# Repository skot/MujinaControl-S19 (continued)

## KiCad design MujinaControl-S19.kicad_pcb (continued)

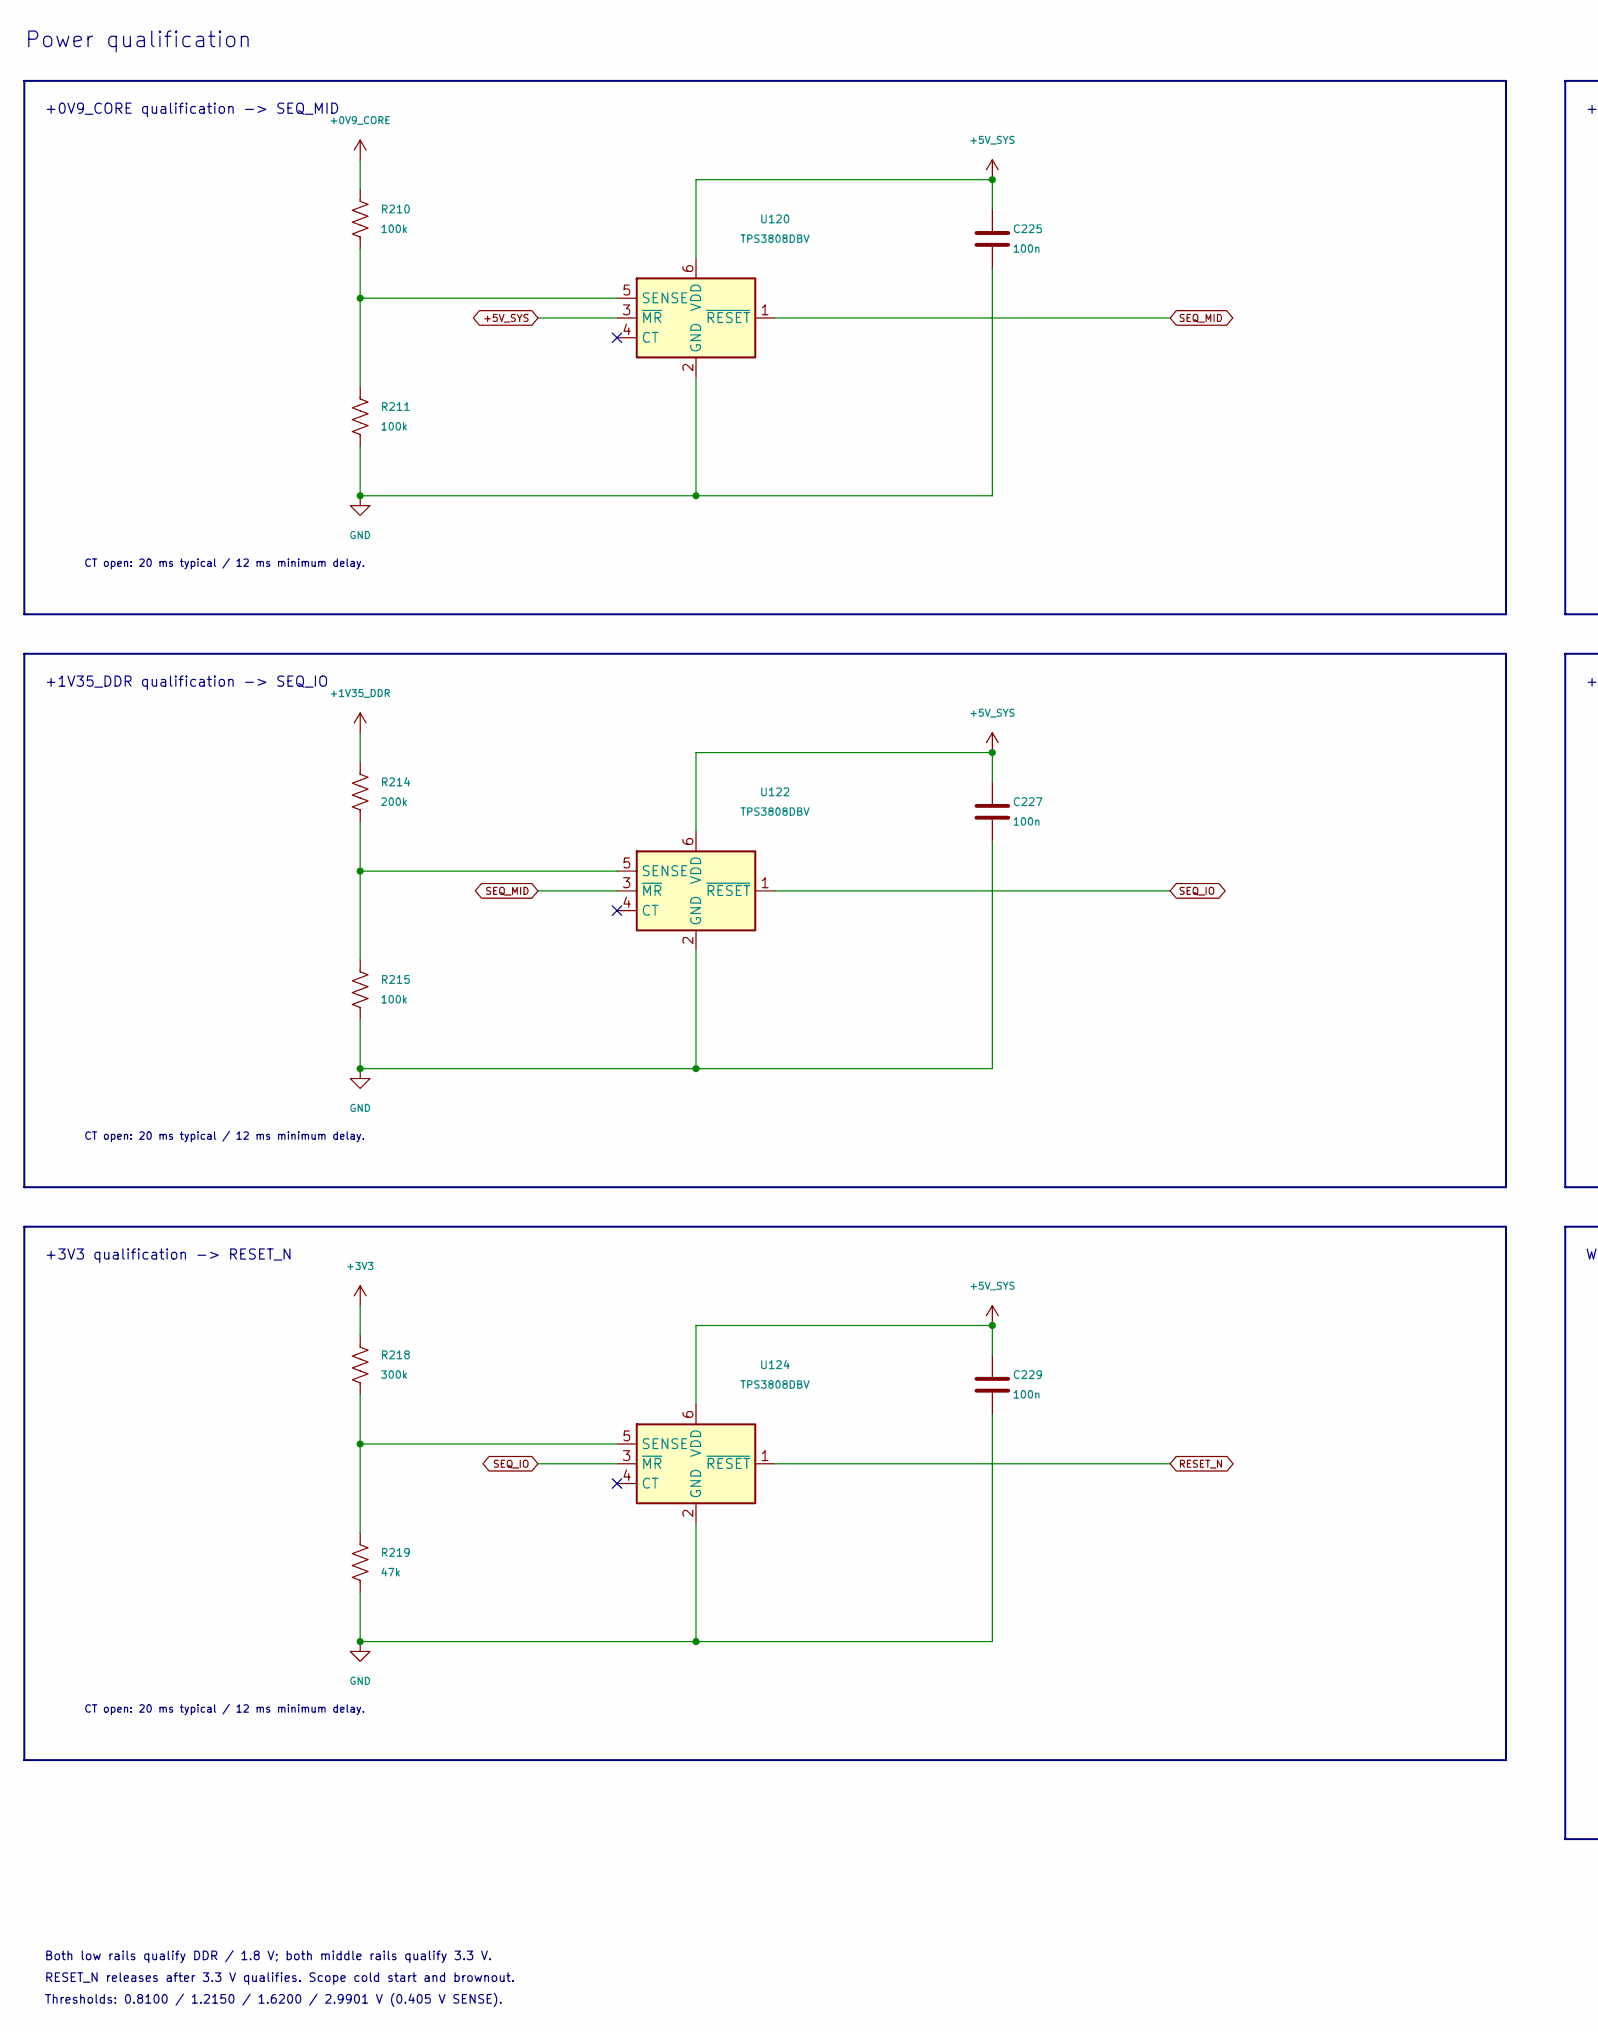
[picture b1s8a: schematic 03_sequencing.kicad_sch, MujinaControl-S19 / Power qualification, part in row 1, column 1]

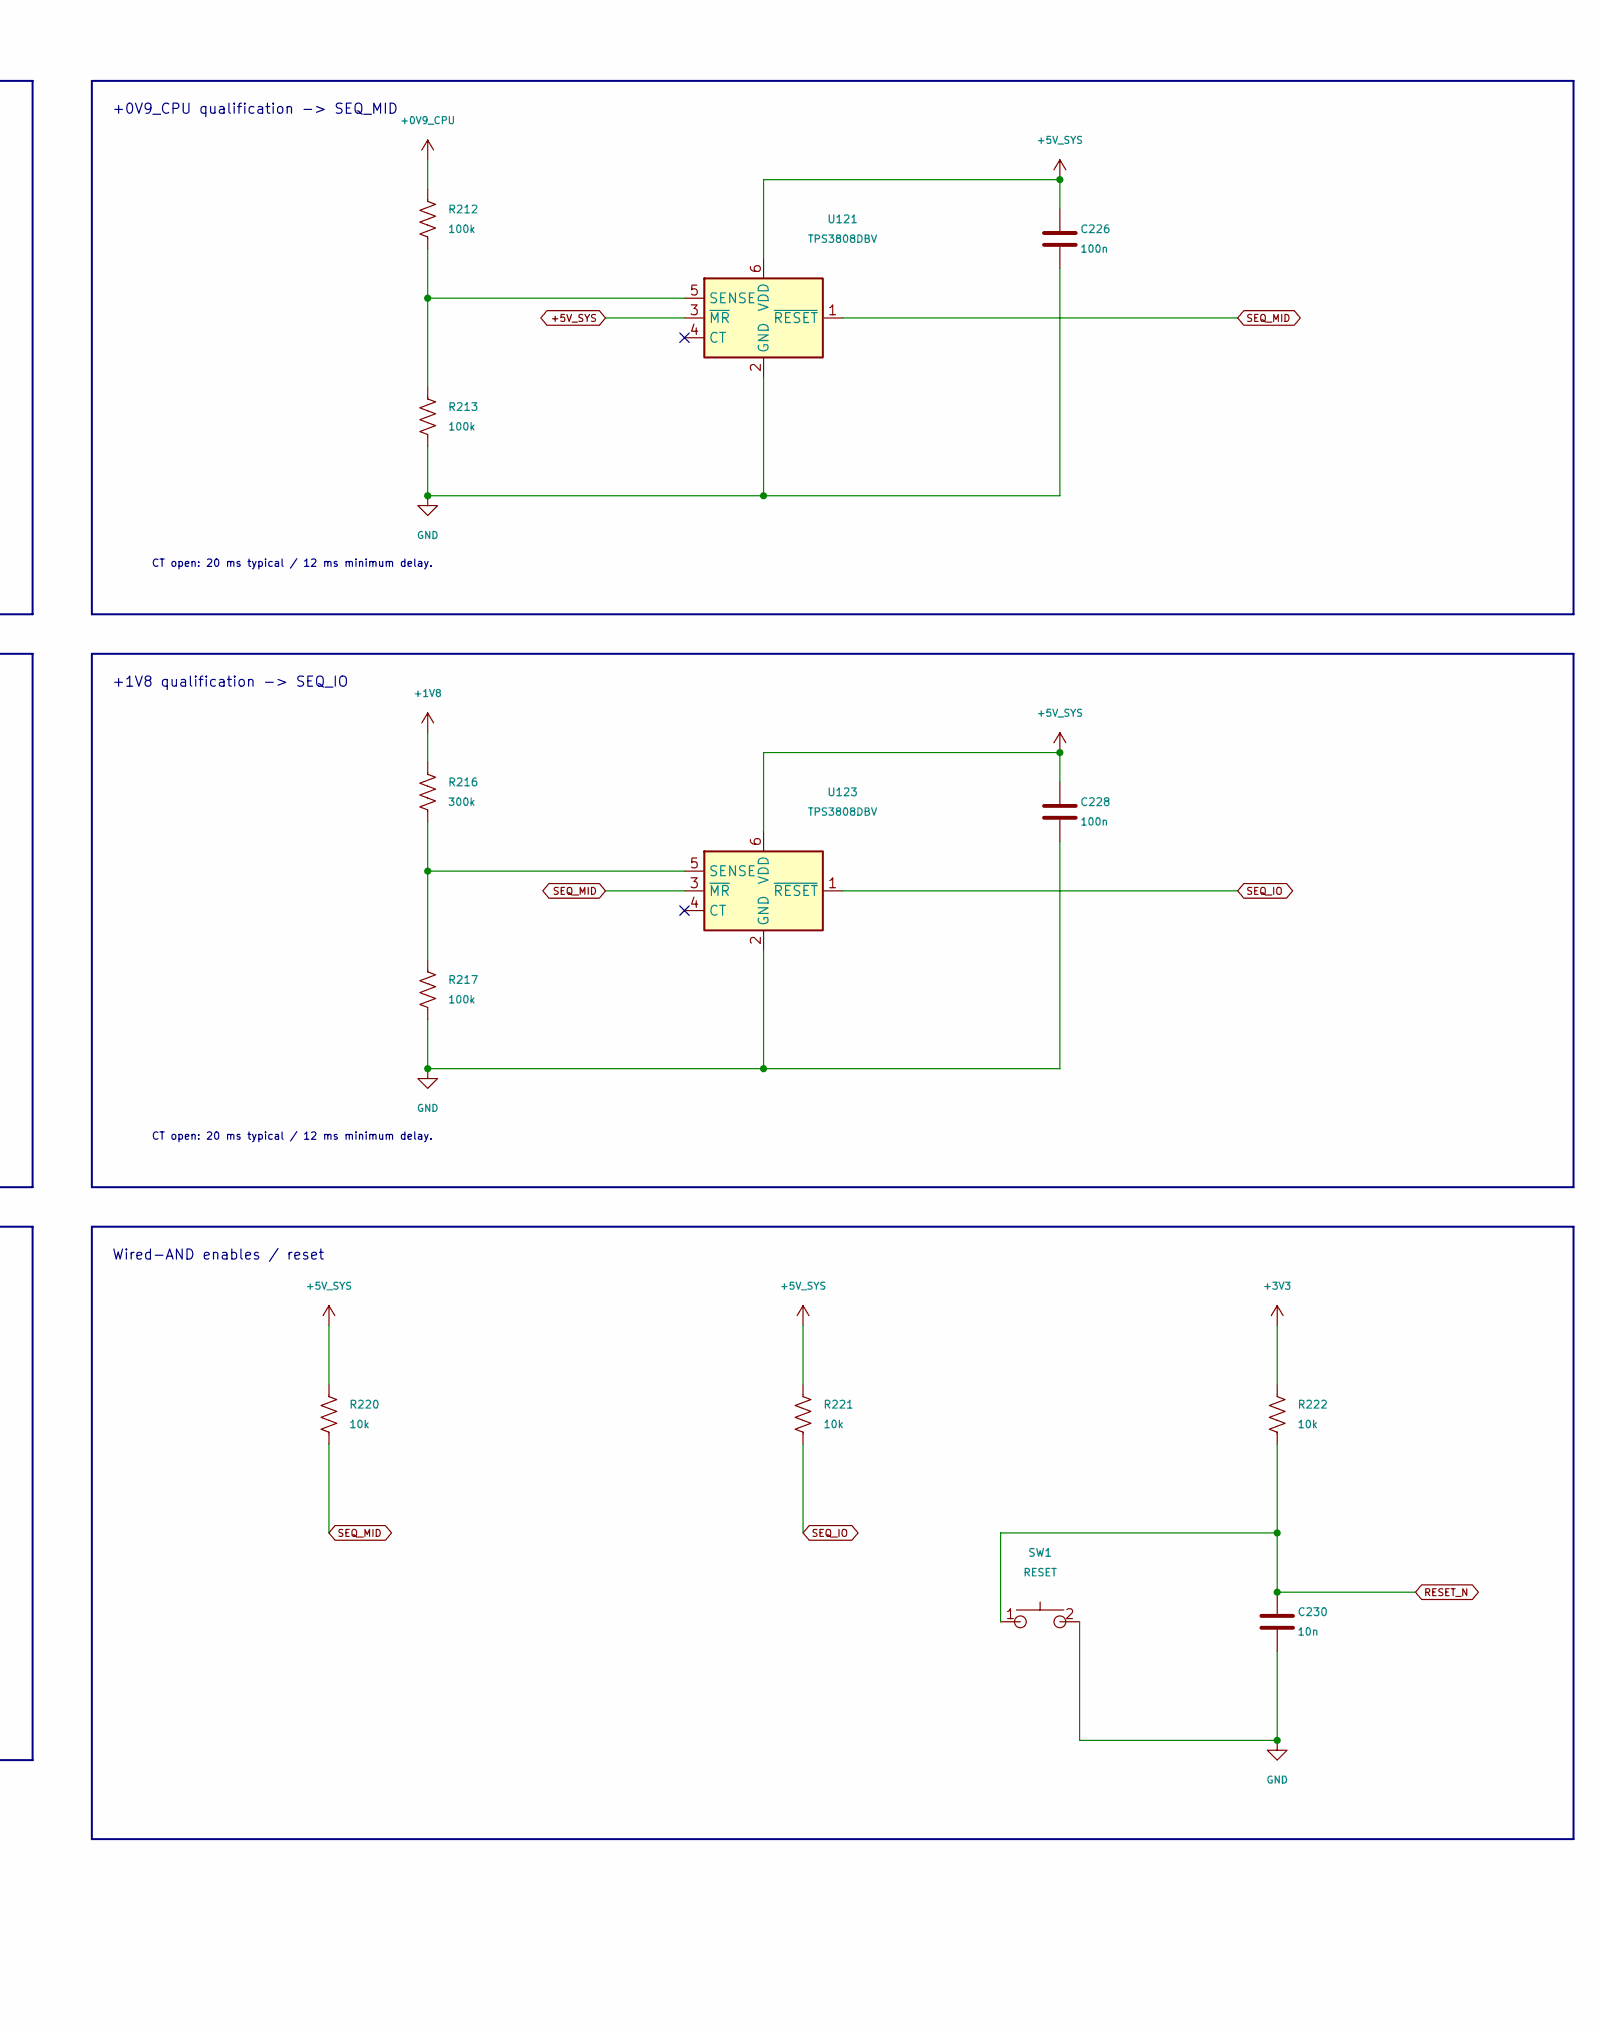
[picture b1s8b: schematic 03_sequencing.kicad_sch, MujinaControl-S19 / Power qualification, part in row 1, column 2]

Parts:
C225, C226, C227, C228, C229: 100n; C_0402_1005Metric; MPN CL05B104KO5NNNC; LCSC C1525
C230: 10n; C_0402_1005Metric; MPN CL05B103KB5NNNC; LCSC C15195
R210, R211, R212, R213, R215, R217: 100k; R_0402_1005Metric; MPN 0402WGF1003TCE; LCSC C25741
R214: 200k; R_0402_1005Metric; MPN 0402WGF2003TCE; LCSC C25764
R216, R218: 300k; R_0402_1005Metric; MPN 0402WGF3003TCE; LCSC C25774
R219: 47k; R_0402_1005Metric; MPN 0402WGF4702TCE; LCSC C25792
R220, R221, R222: 10k; R_0402_1005Metric; MPN 0402WGF1002TCE; LCSC C25744
SW1: RESET; SW-SMD_TC-S3601-3.5-260G-F0.6; MPN TC-S3601-3.5-260G-F0.6; LCSC C49101620
U120, U121, U122, U123, U124: TPS3808DBV; SOT-23-6; MPN TPS3808G01DBVR-TP; LCSC C42394092

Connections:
+0V9_CORE: R210.1; also elsewhere on the board
+0V9_CPU: R212.1; also elsewhere on the board
+1V8: R216.1; also elsewhere on the board
+1V35_DDR: R214.1; also elsewhere on the board
+3V3: R218.1, R222.1; also elsewhere on the board
+5V_SYS: C225.1, C226.1, C227.1, C228.1, C229.1, R220.1, R221.1, U120.3 (~MR), U120.6 (VDD), U121.3 (~MR), U121.6 (VDD), U122.6 (VDD), U123.6 (VDD), U124.6 (VDD); also elsewhere on the board
GND: C225.2, C226.2, C227.2, C228.2, C229.2, C230.2, R211.2, R213.2, R215.2, R217.2, R219.2, SW1.2, U120.2 (GND), U121.2 (GND), U122.2 (GND), U123.2 (GND), U124.2 (GND); also elsewhere on the board
unnamed: R210.2, R211.1, U120.5 (SENSE)
unnamed: R212.2, R213.1, U121.5 (SENSE)
unnamed: R214.2, R215.1, U122.5 (SENSE)
unnamed: R216.2, R217.1, U123.5 (SENSE)
unnamed: R218.2, R219.1, U124.5 (SENSE)
RESET_N: C230.1, R222.2, SW1.1, U124.1 (~RESET); also elsewhere on the board
SEQ_IO: R221.2, U122.1 (~RESET), U123.1 (~RESET), U124.3 (~MR); also elsewhere on the board
SEQ_MID: R220.2, U120.1 (~RESET), U121.1 (~RESET), U122.3 (~MR), U123.3 (~MR); also elsewhere on the board

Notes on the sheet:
Wired-AND enables / reset
+1V8 qualification -> SEQ_IO
+0V9_CPU qualification -> SEQ_MID
+1V35_DDR qualification -> SEQ_IO
Thresholds: 0.8100 / 1.2150 / 1.6200 / 2.9901 V (0.405 V SENSE).
+3V3 qualification -> RESET_N
+0V9_CORE qualification -> SEQ_MID
Both low rails qualify DDR / 1.8 V; both middle rails qualify 3.3 V.
RESET_N releases after 3.3 V qualifies. Scope cold start and brownout.
Power qualification
CT open: 20 ms typical / 12 ms minimum delay.

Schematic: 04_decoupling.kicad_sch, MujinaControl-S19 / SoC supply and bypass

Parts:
C231, C232, C233, C234, C235, C236, C237, C238, C239, C241, C243, C244, C245, C247, C248, C249, C250, C251, C252, C253, C255, C256, C257, C258, C262, C263, C265: 100n; C_0402_1005Metric; MPN CL05B104KO5NNNC; LCSC C1525
C240, C242, C246, C254, C259, C260: 10u; C_0805_2012Metric; MPN CL21A106KAYNNNE; LCSC C15850
C261, C264, C266, C267: 1u; C_0402_1005Metric; MPN CL05A105KA5NQNC; LCSC C52923
FB201, FB202: 120R @ 100MHz; L_0402_1005Metric; MPN BLM15AG121SN1D; LCSC C85812
FID1, FID2, FID3: Fiducial; Fiducial_1mm_Mask2mm
H1, H2, H3, H4: MountingHole_Pad; MountingHole_3mm_Pad; MPN PCB_MOUNTING_HOLE; LCSC N/A
H5: MountingHole_Pad; MountingHole_3.5mm_Pad; MPN PCB_MOUNTING_HOLE; LCSC N/A
R223: 1; R_0402_1005Metric; MPN 0402WGF100KTCE; LCSC C25086
R224: 100; R_0402_1005Metric; MPN 0402WGF1000TCE; LCSC C25076
U100: RV1106G2; Rockchip_QFN-128-1EP_12.3x12.3mm_P0.35mm_EP7x7mm; MPN RV1106G2; LCSC C5272606

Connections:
+0V9_CORE: C231.1, C232.1, C233.1, C234.1, C235.1, C236.1, C237.1, C238.1, C239.1, C240.1, C260.1, U100.10 (DVDD_1), U100.51 (DVDD_2), U100.54 (DVDD_3), U100.55 (DVDD_4), U100.67 (PMU_DVDD0V9), U100.71 (OSC_PLL_DVDD), U100.82 (DVDD_5), U100.103 (DVDD_6), U100.116 (DVDD_7); also elsewhere on the board
+0V9_CPU: C241.1, C242.1, C261.1, U100.115 (CPU_DVDD); also elsewhere on the board
+1V8: C255.1, C256.1, C257.1, C258.1, C259.1, FB201.1, R223.1, U100.1 (MIPI_AVDD1V8), U100.31 (CODEC_AVDD1V8), U100.53 (DDR_PLL_AVDD1V8), U100.70 (OSC_AVDD1V8); also elsewhere on the board
+1V35_DDR: C243.1, C244.1, C245.1, C246.1, U100.49 (DDR_VDDQ_1), U100.50 (DDR_VDDQ_2), U100.56 (DDR_VDDQ_3); also elsewhere on the board
+3V3: C247.1, C248.1, C249.1, C250.1, C251.1, C252.1, C253.1, C254.1, FB202.1, R224.1, U100.13 (GPIO4_VCC), U100.28 (USB_AVDD3V3), U100.43 (GPIO3_VCC), U100.61 (PMU_VCC3V3), U100.81 (GPIO1_VCC3V3), U100.88 (GPIO6_VCC), U100.108 (GPIO5_VCC); also elsewhere on the board
ETH_1V8: C263.1, C264.1, FB201.2, U100.96 (OTP_AVDD1V8)
ETH_3V3: C265.1, C266.1, FB202.2, U100.101 (ETH_AVDD3V3)
GND: C231.2, C232.2, C233.2, C234.2, C235.2, C236.2, C237.2, C238.2, C239.2, C240.2, C241.2, C242.2, C243.2, C244.2, C245.2, C246.2, C247.2, C248.2, C249.2, C250.2, C251.2, C252.2, C253.2, C254.2, C255.2, C256.2, C257.2, C258.2, C259.2, C260.2, C261.2, C262.2, C263.2, C264.2, C265.2, C266.2, C267.2, H1.1 (1_1), H2.1 (1_1), H3.1 (1_1), H4.1 (1_1), H5.1 (1_1), U100.37 (GND), U100.57 (GND), U100.129 (GND_EP); also elsewhere on the board
RTC_3V3: C267.1, R224.2, U100.19 (RTC_AVDD3V3)
USB_1V8: C262.1, R223.2, U100.24 (SARADC_USB_AVDD1V8)

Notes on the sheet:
H1-H4: 3.0 mm holes. H5: 3.5 mm hole beside the Ethernet jack.
DDR3L: 1.35 V
CPU supply
Place each ceramic at its supply pin. Tie all ground pins and EP129
Bare 1 mm copper dots, 2 mm mask opening, top side: not in the parts list.
SoC supply and bypass
1.8 V analog / I/O
ETH_1V8 also supplies OTP / TSADC; place bead at pin 96.
to solid ground planes. RTC 100R / 1u is required by Rockchip.
U100 power distribution / exposed pad
Bulk / filtered analog rails
Core: one 100n per supply pin
Chassis mounting pads
3.3 V I/O
Assembly fiducials

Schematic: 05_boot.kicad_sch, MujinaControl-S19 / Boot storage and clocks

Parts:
C268, C271: 100n; C_0402_1005Metric; MPN CL05B104KO5NNNC; LCSC C1525
C269, C277: 1u; C_0402_1005Metric; MPN CL05A105KA5NQNC; LCSC C52923
C270: 10u; C_0805_2012Metric; MPN CL21A106KAYNNNE; LCSC C15850
C272, C273, C274, C275: 18p; C_0402_1005Metric; MPN 0402CG180J500NT; LCSC C1549
C276: 1n; C_0402_1005Metric; MPN 0402B102K500NT; LCSC C1523
J16: UART2 DEBUG; PinHeader_1x03_P2.54mm_Vertical; MPN 61300311121; LCSC C2915006
J18: JTAG; PinHeader_1x05_P2.54mm_Vertical; MPN 61300511121; LCSC C6461551; not fitted
J101: Micro_SD_Card_Det2; microSD_HC_Hirose_DM3D-SF; MPN DM3D-SF; LCSC C719027
R225, R235, R236: 22; R_0402_1005Metric; MPN 0402WGF220JTCE; LCSC C25092
R226, R227, R228, R229, R230, R231, R232, R233, R234, R238, R240: 10k; R_0402_1005Metric; MPN 0402WGF1002TCE; LCSC C25744
R237: 1M; R_0402_1005Metric; MPN 0402WGF1004TCE; LCSC C26083; not fitted
R239: 100; R_0402_1005Metric; MPN 0402WGF1000TCE; LCSC C25076
R241: 240; R_0402_1005Metric; MPN RC0402FR-07240RL; LCSC C114755
SW2: BOOT; SW-SMD_TC-S3601-3.5-260G-F0.6; MPN TC-S3601-3.5-260G-F0.6; LCSC C49101620
U130: W25N02KVZEIR; WSON-8-1EP_8x6mm_P1.27mm_EP3.4x4.3mm; MPN W25N02KVZEIR; LCSC C3010298
Y100: 24MHz / CL12pF; Crystal_SMD_3225-4Pin_3.2x2.5mm; MPN X322524MOB4SI; LCSC C70590
Y101: 32.768kHz / CL12.5pF; Crystal_SMD_3215-2Pin_3.2x1.5mm; MPN Q13FC13500004; LCSC C32346

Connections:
+1V8: R238.1; also elsewhere on the board
+3V3: C268.1, C269.1, C270.1, C271.1, J18.1, J101.4 (VDD), R226.1, R227.1, R228.1, R229.1, R230.1, R231.1, R232.1, R233.1, R234.1, R240.1, U130.8 (VCC); also elsewhere on the board
BOOT_ADC: C276.1, R238.2, R239.1; also elsewhere on the board
CODEC_VCM: C277.1; also elsewhere on the board
DEBUG_RX: J16.3, R240.2; also elsewhere on the board
DEBUG_TX: J16.1; also elsewhere on the board
DRAM_ZQ: R241.1; also elsewhere on the board
FSPI_CLK: R225.2, U130.6 (SCLK)
FSPI_CLK_SOC: R225.1; also elsewhere on the board
FSPI_CS_N: R226.2, U130.1 (~CS); also elsewhere on the board
FSPI_D0: U130.5 (SI/IO0); also elsewhere on the board
FSPI_D1: U130.2 (SO/IO1); also elsewhere on the board
FSPI_D2: R227.2, U130.3 (~WP/IO2); also elsewhere on the board
FSPI_D3: R228.2, U130.7 (~HOLD/~RESET/IO3); also elsewhere on the board
GND: C268.2, C269.2, C270.2, C271.2, C272.2, C273.2, C274.2, C275.2, C276.2, C277.2, J16.2, J18.5, J101.6 (VSS), J101.10 (DET_A), J101.SH (SHIELD), R241.2, SW2.2, U130.4 (VSS), U130.9 (PAD), Y100.2 (G), Y100.4 (G); also elsewhere on the board
unnamed: C272.1, R236.2, Y100.1
unnamed: R239.2, SW2.1
OSC_XIN: C273.1, R237.2, Y100.3; also elsewhere on the board
OSC_XOUT: R236.1, R237.1; also elsewhere on the board
RTC_XIN: C274.1, Y101.1; also elsewhere on the board
RTC_XOUT: C275.1, Y101.2; also elsewhere on the board
SD_CLK: J101.5 (CLK), R235.2
SD_CLK_SOC: R235.1; also elsewhere on the board
SD_CMD: J101.3 (CMD), R229.2; also elsewhere on the board
SD_D0: J101.7 (DAT0), R230.2; also elsewhere on the board
SD_D1: J101.8 (DAT1), R231.2; also elsewhere on the board
SD_D2: J18.3, J101.1 (DAT2), R232.2; also elsewhere on the board
SD_D3: J18.2, J101.2 (DAT3/CD), R233.2; also elsewhere on the board
SD_DET_N: J101.9 (DET_B), R234.2; also elsewhere on the board

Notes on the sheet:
18p crystal loads assume ~3p parasitic: measure startup and frequency.
Main oscillator / RTC crystal
Boot storage and clocks
BOOT key / UART debug / JTAG header / bias
J16: 1 = SoC TX; 2 = GND; 3 = SoC RX. 3.3 V only.
microSD - development / alternate boot
J18 (not fitted): 1 = 3.3 V reference; 2 = TMS (SD_D3); 3 = TCK (SD_D2); 4 = RESET_N; 5 = GND.
256 MB SPI NAND - normal boot
JTAG is an alternate function of the SD_D2 / SD_D3 pins (JTAG_CPU_TCK_M0 / TMS_M0): use it with no microSD card inserted.
SPI NAND has priority over SD. Hold BOOT during reset for USB recovery.
CPU JTAG, 2-wire - not fitted

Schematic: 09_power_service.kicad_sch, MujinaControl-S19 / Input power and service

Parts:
C283, C303, C304, C305: 100n; C_0402_1005Metric; MPN CL05B104KO5NNNC; LCSC C1525
C284, C285: 10u / 50V; C_1210_3225Metric; MPN CL32B106KBJNNNE; LCSC C138687
C286, C302: 100n / 50V; C_0402_1005Metric; MPN CL05B104KB54PNC; LCSC C307331
C287, C288: 22u / 25V; C_0805_2012Metric; MPN CL21A226MAQNNNE; LCSC C45783
C301: 33n / 50V; C_0603_1608Metric; MPN CL10B333KB8NNNC; LCSC C21117
D2: BZX84C12; SOT-23-3_L2.9-W1.6-P1.90-LS2.8-BR; MPN BZX84C12; LCSC C19077471
D220: SMBJ15A; D_SMB; MPN SMBJ15A; LCSC C19077569
J1: 0455580003; CONN-TH_50362462; MPN 50362462; LCSC C492365
J10: PSU Comm; CONN-TH_6P-P2.00_PHD-2X3A; MPN HC-PHD-2*3A; LCSC C2845614
J15: ACC 2x7 / 0.1 in; PinHeader_2x07_P2.54mm_Vertical; MPN PZ254V-12-14P; LCSC C492424; not fitted
L210: 1.5u; IND-SMD_L2.0-W1.6; MPN FTC201612S1R5MBCA; LCSC C5832350
Q1: SiSS27DN-T1-GE3; onsemi_WDFN-8_3.3x3.3mm_P0.65mm_CASE483AW; MPN SiSS27DN-T1-GE3; LCSC C506609
R270, R279: 10k; R_0402_1005Metric; MPN 0402WGF1002TCE; LCSC C25744
R271: 100k; R_0402_1005Metric; MPN 0402WGF1003TCE; LCSC C25741
R272, R273: 4.7k; R_0402_1005Metric; MPN 0402WGF4701TCE; LCSC C25900; not fitted
R282, R284: 27k; R_0402_1005Metric; MPN 0402WGF2702TCE; LCSC C25771
R283, R285: 5.1k; R_0402_1005Metric; MPN 0402WGF5101TCE; LCSC C25905
R286, R287: 4.7k; R_0402_1005Metric; MPN 0402WGF4701TCE; LCSC C25900
TP29, TP30: TestPoint; TestPoint_Pad_D1.0mm; MPN PCB_TESTPOINT; LCSC N/A
U115: TPS62933DRLR; SOT-583-8_L2.1-W1.2-P0.50-LS1.6-BR; MPN TPS62933DRLR; LCSC C3200405

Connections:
+1V8: C305.1, J15.7; also elsewhere on the board
+3V3: C304.1, J15.2, R272.1, R273.1, R286.1, R287.1; also elsewhere on the board
+5V_SYS: C287.1, C288.1, C303.1, J15.1, L210.2, R282.1; also elsewhere on the board
+12V_FAN: C283.1, C284.1, C285.1, C302.1, D2.3 (K), D220.1 (K), Q1.1 (S), Q1.2 (S), Q1.3 (S), R284.1, U115.3 (VIN); also elsewhere on the board
+12V_IN: J1.1, J1.2, J1.3, Q1.5 (D), Q1.6 (D), Q1.7 (D), Q1.8 (D)
ACC1V8_GPIO3_C7: J15.9; also elsewhere on the board
ACC1V8_GPIO3_D0: J15.10; also elsewhere on the board
ACC1V8_GPIO3_D1: J15.11; also elsewhere on the board
ACC1V8_GPIO3_D2: J15.12; also elsewhere on the board
ACC1V8_GPIO3_D3: J15.13; also elsewhere on the board
ACC_GPIO4_A7: J15.5; also elsewhere on the board
ACC_I2C4_SCL: J15.3, R286.2; also elsewhere on the board
ACC_I2C4_SDA: J15.4, R287.2; also elsewhere on the board
GND: C283.2, C284.2, C285.2, C287.2, C288.2, C301.2, C302.2, C303.2, C304.2, C305.2, D220.2 (A), J1.4, J1.5, J1.6, J10.2, J15.6, J15.8, J15.14, R270.2, R271.2, R279.2, R283.2, R285.2, U115.4 (GND); also elsewhere on the board
unnamed: D2.1 (A), Q1.4 (G), R270.1
unnamed: C286.1, U115.6 (BST)
unnamed: R284.2, R285.1, U115.2 (EN)
unnamed: R282.2, R283.1, U115.8 (FB)
unnamed: R279.1, U115.1 (RT)
unnamed: C301.1, U115.7 (SS)
unnamed: C286.2, L210.1, U115.5 (SW)
PSU_AUX1: J10.1, TP29.1 (1_1)
PSU_AUX4: J10.4, TP30.1 (1_1)
PSU_EN: J10.5, R271.1; also elsewhere on the board
PSU_SCL: J10.6, R273.2; also elsewhere on the board
PSU_SDA: J10.3, R272.2; also elsewhere on the board

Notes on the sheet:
Controller branch / 5 V preregulator
5.6 mOhm max at VGS=-10 V; estimated hot loss ~1.6 W at 14 A.
9 / 10 : GPIO3_C7 / D0 : UART5 TX / RX (M2), or I2C4 SCL / SDA (M2), 1.8 V
J1 retains the six-pin bitcrane power connector. Q1 protects both fan and controller supplies from reversed input. No onboard fuse: input fault disconnection relies on upstream protection.
No series, ESD or current-limit parts: no hot-plugging, keep loads small.
Bonanza 10k RT: 1.98 MHz; 33n SS: 4.8 ms.
I2C4 (3 / 4) has 4.7k pull-ups; the other signals go straight to the SoC.
3.3 V
The other GPIOs of the former 2x20 header serve fans, WiFi and hashboard power.
Input power and service
Dedicated drain heat spreaders; qualify Tj <=125 C at 40 C ambient.
J15: 2x7 0.1 in accessory header (14 pins).
Pin functions
5 : GPIO4_A7 : I2C2 SCL (M1), SPI1 CLK, 3.3 V
Qualify transient, thermal and overload behavior.
Q1 design target: 14 A = four 3 A fans + 2 A controller allowance.
3 / 4 : GPIO2_A1 / A0 : I2C4 SCL / SDA (M0), 3.3 V
PSU communication / enable defaults low
1 : +5V_SYS; 2 : +3V3; 6 / 8 / 14 : GND; 7 : +1V8 reference
12 V input / reverse-polarity protection / fan supply
Reverse-polarity protection retained; no inrush or current limiting.
J15 notes
Pins 3 / 4 / 5: 3.3 V signals. Pins 9-13: 1.8 V ONLY.
J15 is not fitted at assembly: solder a 2x7 header if it is needed.
Accessory header J15 / spare SoC I/O
+1V8 (pin 7) is a level-shifter reference only, not a supply.
No PWM output is left on this header (PWM1 drives fan 4).
27k / 5.1k EN divider: starts near 7.6 V input.
11 / 12 : GPIO3_D1 / D2 : UART5 RTS / CTS (M2), or I2C3 SCL / SDA (M2), 1.8 V
1.8 V ONLY
Confirm PSU enable polarity and cable-side pull-ups before fitting R272/R273. Hashboard bias is on sheet 8.
13 : GPIO3_D3 : GPIO, 1.8 V
5.035 V / 2 A system budget; fan current bypasses U115.
No direct 12 V connection to EN (5.5 V limit).

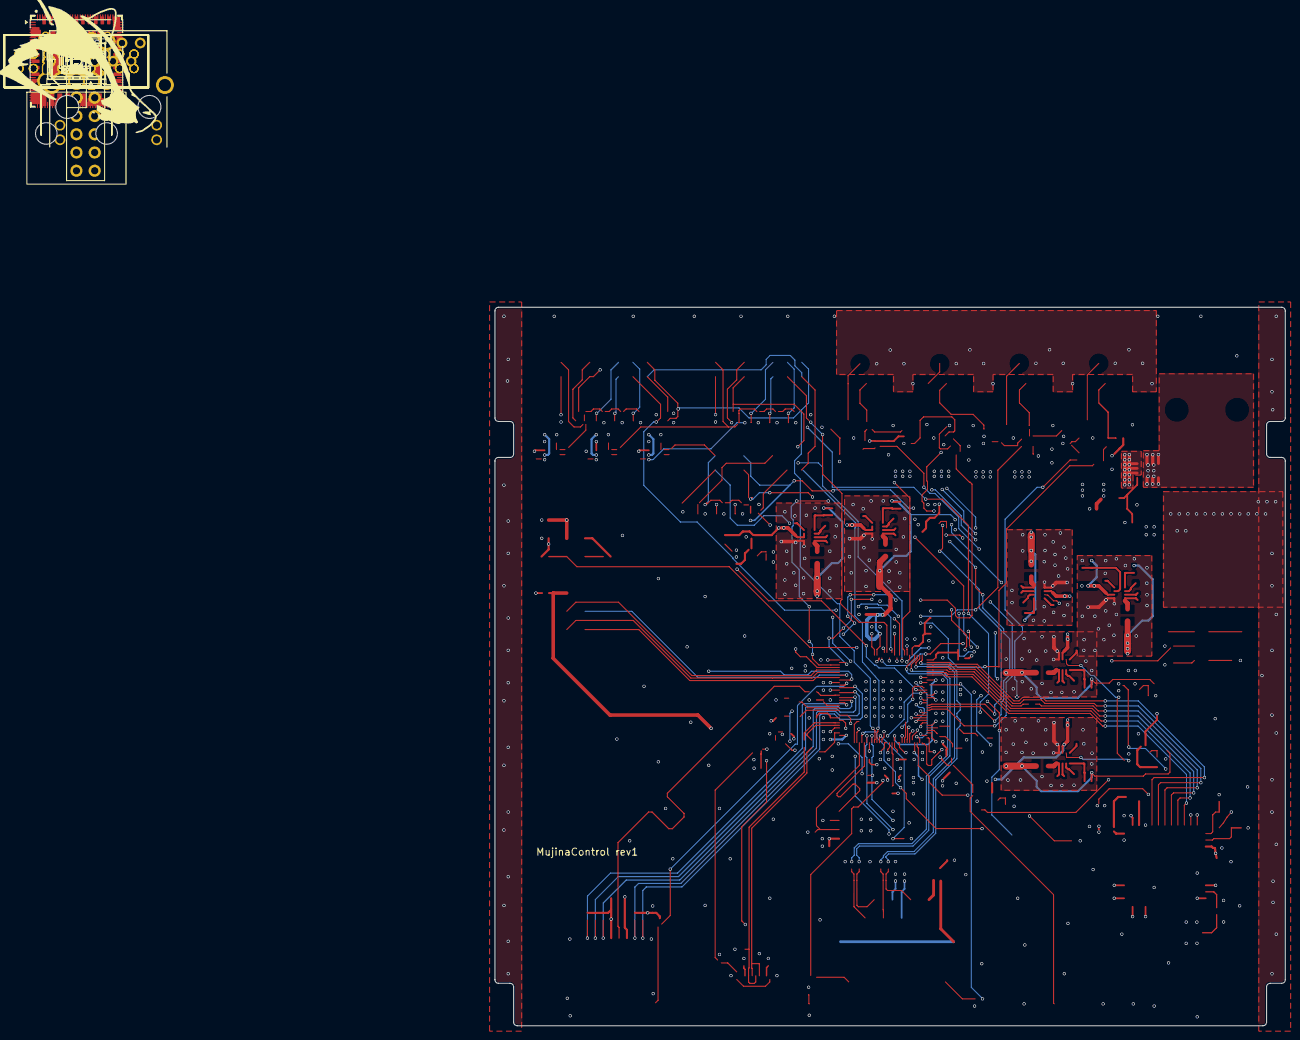
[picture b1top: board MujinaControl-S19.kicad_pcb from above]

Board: 6 copper layers, 110.0 x 100.0 mm, 329 parts (0 on the bottom side), 186 nets.

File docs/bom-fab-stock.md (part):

# Parts against the fab's stock — 2026-11-12

The board is assembled by the fab, so every purchased part carries the fab part number (`LCSC` field) and an `MPN` field, and uses a basic-category part wherever one exists in the same footprint with the same value and an equal or better rating.

Live stock was read on 2026-11-12 for every part number. Stock is a reading, not a reservation.

## Result

- 310 symbols: 304 purchased parts, all with both fields; the six others are the four mounting holes and two test pads (`N/A`).
- 65 part numbers: **24 basic, 9 preferred (no fee), 32 extended.** Before this pass: 70 part numbers, 7 basic, 2 preferred, 61 extended.
- Of 287 fitted placements, 206 are basic, 20 preferred, 61 extended.
- The RV1106G2 is listed for standard assembly only, so the whole order goes through the fab's standard (not economic) assembly service.

## Changed in this pass

| Was | Now | Parts | Note |
|---|---|---|---|
| C71629 GRM155R71C104KA88D | C1525 CL05B104KO5NNNC | 39 × 100 nF 0402 | basic; same 16 V X7R |
| C76999 GRM155R61A105KE15D | C52923 CL05A105KA5NQNC | 13 × 1 µF 0402 | basic; 25 V X5R (was 10 V) |
| C77073 GRM21BR61A106KE19L | C15850 CL21A106KAYNNNE | 7 × 10 µF 0805 | basic; 25 V X5R (was 10 V) |
| C77177 GRM1555C1H101JA01D | C1546 0402CG101J500NT | 4 × 100 pF 0402 | basic; same 50 V C0G 5 % |
| C33149 GRM1555C1H180JA01D | C1549 0402CG180J500NT | 4 × 18 pF 0402 | basic; same 50 V C0G 5 % |
| C77019 GRM155R71H103KA88D | C15195 CL05B103KB5NNNC | 3 × 10 nF 0402 | basic; same 50 V X7R |
| C77018 GRM155R71H102KA01D | C1523 0402B102K500NT | 1 × 1 nF 0402 | basic; same 50 V X7R |
| C97973 GRM32ER7YA106KA12L | C138687 CL32B106KBJNNNE | C284, 10 µF 1210 | still extended; now the same part as C285 (50 V X7R, was 35 V), one extended line fewer |
| C105871 RC0402FR-074K7L | C25900 0402WGF4701TCE | 36 × 4.7 k | basic |
| C60490 RC0402FR-0710KL | C25744 0402WGF1002TCE | 23 × 10 k | basic |
| C60491 RC0402FR-07100KL | C25741 0402WGF1003TCE | 17 × 100 k | basic |
| C60485 RC0402JR-070RL | C17168 0402WGF0000TCE | 7 × 0 Ω | basic |
| C106235 RC0402FR-071KL | C11702 0402WGF1001TCE | 5 × 1 k | basic |
| C114765 RC0402FR-0722RL | C25092 0402WGF220JTCE | 3 × 22 Ω | basic |
| C106232 RC0402FR-07100RL | C25076 0402WGF1000TCE | 2 × 100 Ω | basic |
| C138033 RC0402FR-071ML | C26083 0402WGF1004TCE | 2 × 1 M (not fitted) | basic |
| C276273 RC0402FR-07510RL | C25123 0402WGF5100TCE | 2 × 510 Ω | basic |
| C105872 RC0402FR-075K1L | C25905 0402WGF5101TCE | 2 × 5.1 k | basic; merges with R283/R285 |
| C138044 RC0402FR-0718KL | C25762 0402WGF1802TCE | R255, 18 k | preferred (no fee) |
| C185446 RC0402FR-071RL | C25086 0402WGF100KTCE | R223, 1 Ω | preferred (no fee) |
| C138062 RC0402FR-07124KL | C36777 0402WGF1243TCE | R208, 124 k | still extended; old part had 15 in stock, new one 117 k |
| C185443 RC0402FR-07215KL (215 k) | C25764 0402WGF2003TCE (200 k) | R214 | basic; value changed, see the trip-point section |
| C138065 RC0402FR-07110KL (110 k) | C25741 0402WGF1003TCE (100 k) | R210, R212 | basic; value changed |
| C226987 316 k, C227183 665 k | C25774 0402WGF3003TCE (300 k) | R216, R218 | preferred (no fee); value changed |
| C25741 100 k | C25792 0402WGF4702TCE (47 k) | R219 | basic; value changed |
| C130253 ABS07-32.768KHZ-T | C32346 Q13FC13500004 | Y101, 32.768 kHz 3215 | basic; same 12.5 pF load, ±20 ppm, 70 kΩ ESR |
| C19653 TPS3808G01DBVR | C42394092 TPS3808G01DBVR-TP | U120–U124 | TI ordering code had **0** in stock; second-source part chosen for stock (6,283), see the supervisor section below |

All resistors are 0402, 1 %, 62.5 mW, as before. Footprints and nets are unchanged. Values are unchanged except the supervisor dividers (R210, R212, R214, R216, R218, R219, see below) and C284's value text (10u / 35V → 10u / 50V).

## Stock to watch

| Part | Use | Stock | Per board | Note |
|---|---|---|---|---|
| ~~C894097 NTTFS008P03P8Z~~ | Q1 input MOSFET | 7 | 1 | Replaced on 2026-11-14 by C506609 SiSS27DN-T1-GE3 (7,565 in stock), see below. |
| C437089 X2026WV-2x09D-46SN | J3–J5 hashboard connectors | 29 | 3 | Nine boards. Same-series 2×9, 2 mm parts in stock: C2845620 HC-PHD-2*9A (2,413; same maker as J10), C495666 B18B-PHDSS (9,609). Not changed: the footprint should be checked against the chosen part first. |
| C492365 50362462 | J1 power input | 476 | 1 | |
| C5272606 RV1106G2 | U100 | 773 | 1 | Standard assembly only. |
| C2167485 1 nF 2 kV, C3010298 W25N02KVZEIR | C280, U130 | 1,948–1,992 | 1 | |

## Supervisors U120–U124 — second source, 2026-11-12

U120–U124 use C42394092 (TPS3808G01DBVR-TP, TECH PUBLIC), 6,283 in stock, about 0.18 USD each. Its datasheet was read against how the part is used here:

| Needed by the circuit | Datasheet |
|---|---|
| SOT-23-6, pins 1 RESET, 2 GND, 3 MR, 4 CT, 5 SENSE, 6 VDD | same pinout; 2.9 × 1.6 mm body, 0.95 mm pitch |
| Adjustable threshold 0.405 V at SENSE (dividers R210–R219) | adjustable version, 0.405 V; accuracy ±1 % typical, ±2 % limits; hysteresis 1.5 % |
| Runs from +5V_SYS | 1.7–6.5 V supply; 7 V absolute maximum on every pin |
| CT left open | 20 ms delay (12–28 ms) |
| MR tied to +5V_SYS or driven by the previous stage (SEQ_MID, SEQ_IO) | MR low below 0.3 VDD, high above 0.7 VDD, internal 90 kΩ pull-up; must not exceed VDD (it does not here) |
| Open-drain output on a 10 kΩ pull-up (R220–R222) | open drain, 0.4 V at 1 mA; pull-up of 10 kΩ or more |
| Divider impedance up to 75 kΩ | SENSE current ±25 nA (about 0.5 % threshold shift at most) |

These figures are the same as the TI part's, and the document is close to a copy of TI's, so the match is on paper only: the part has not been characterised here. Alternatives with the same pinout and threshold, if the first boards show a sequencing problem: C33144197 TPS3808EG01DBVR (TI's newer version, 1,023 in stock, about 1.58 USD, supply up to 6 V) and C702161 TPS3808G01DBVT (the original TI device, 200 in stock, about 1.38 USD). Either is a field-only change.

## Supervisor trip points lowered — 2026-11-12

Before, each supervisor tripped at about 94 % of its rail and released at about 96 %. With the 0.405 V threshold at its +2 % limit, hysteresis at 3 % and 1 % divider resistors, the release point reached the nominal rail voltage, so a rail sitting slightly low could have held the chain in reset. The dividers now put the trip point at about 90 %:

| Supervisor | Rail (nominal) | Divider, top / bottom | Trip, falling | Release, typical | Release, limits |
|---|---|---|---|---|---|
| U120 | +0V9_CORE (0.899 V) | R210 100 k / R211 100 k (was 110 k / 100 k) | 0.810 V, 90.1 % (was 0.851 V) | 0.822 V, 91.4 % | 0.860 V, 95.6 % |
| U121 | +0V9_CPU (0.899 V) | R212 100 k / R213 100 k (was 110 k / 100 k) | 0.810 V, 90.1 % (was 0.851 V) | 0.822 V, 91.4 % | 0.860 V, 95.6 % |
| U122 | +1V35_DDR (1.345 V) | R214 200 k / R215 100 k (was 215 k / 100 k) | 1.215 V, 90.3 % (was 1.276 V) | 1.233 V, 91.7 % | 1.294 V, 96.2 % |
| U123 | +1V8 (1.792 V) | R216 300 k / R217 100 k (was 316 k / 100 k) | 1.620 V, 90.4 % (was 1.685 V) | 1.644 V, 91.8 % | 1.727 V, 96.4 % |
| U124 | +3V3 (3.307 V) | R218 300 k / R219 47 k (was 665 k / 100 k) | 2.990 V, 90.4 % (was 3.098 V) | 3.035 V, 91.8 % | 3.196 V, 96.6 % |

"Limits" stacks threshold +2 %, hysteresis 3 % and both divider resistors 1 % the wrong way. The release point now stays 3.4 % or more below nominal even then, and about 8 % below in the typical case. The lowest trip with everything the other way is 0.786 V, 1.18 V, 1.57 V and 2.88 V.

The 3.3 V supervisor needed both resistors changed: no stocked no-fee value gives 90 % against a 100 k bottom resistor. 300 k / 47 k also brings its divider impedance down from 87 kΩ to 41 kΩ. The sheet note on `03_sequencing.kicad_sch` lists the new thresholds.
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
